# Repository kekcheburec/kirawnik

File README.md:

# kirawnik

> From Belarusian: head, manager

Compact ESP32-C6 board for powering on or rebooting a Framework Desktop over Zigbee or Wi-Fi.

## Overview

kirawnik sits between the motherboard and the case power button cable. It uses the 5V SB pin exposed on the Framework Desktop front panel connector, keeping the ESP32-C6 powered even while the system is shut down or asleep.

For easier installation, the board has silkscreen markings for the cable connections. The external antenna should be connected to the uFL (a.k.a u.FL / IPX / IPEX) connector and mounted on non-metal parts.

Firmware can be built manually or with ESPHome. With ESP32-C6 Zigbee support, the board can connect to many smart home systems and work offline.

## References

- [Front panel connector location and pinout](https://knowledgebase.frame.work/front-panel-io-connectors-amd-ryzen-ai-max-300-series-Hk3SXolHxg)
- [Framework Desktop motherboard connector schematic](https://github.com/FrameworkComputer/Framework-Desktop/blob/main/Mainboard/Mainboard_Interfaces_Schematic_Framework_Desktop_Ryzen_AI_Max.pdf)

## Disclaimer

No warranties of any kind

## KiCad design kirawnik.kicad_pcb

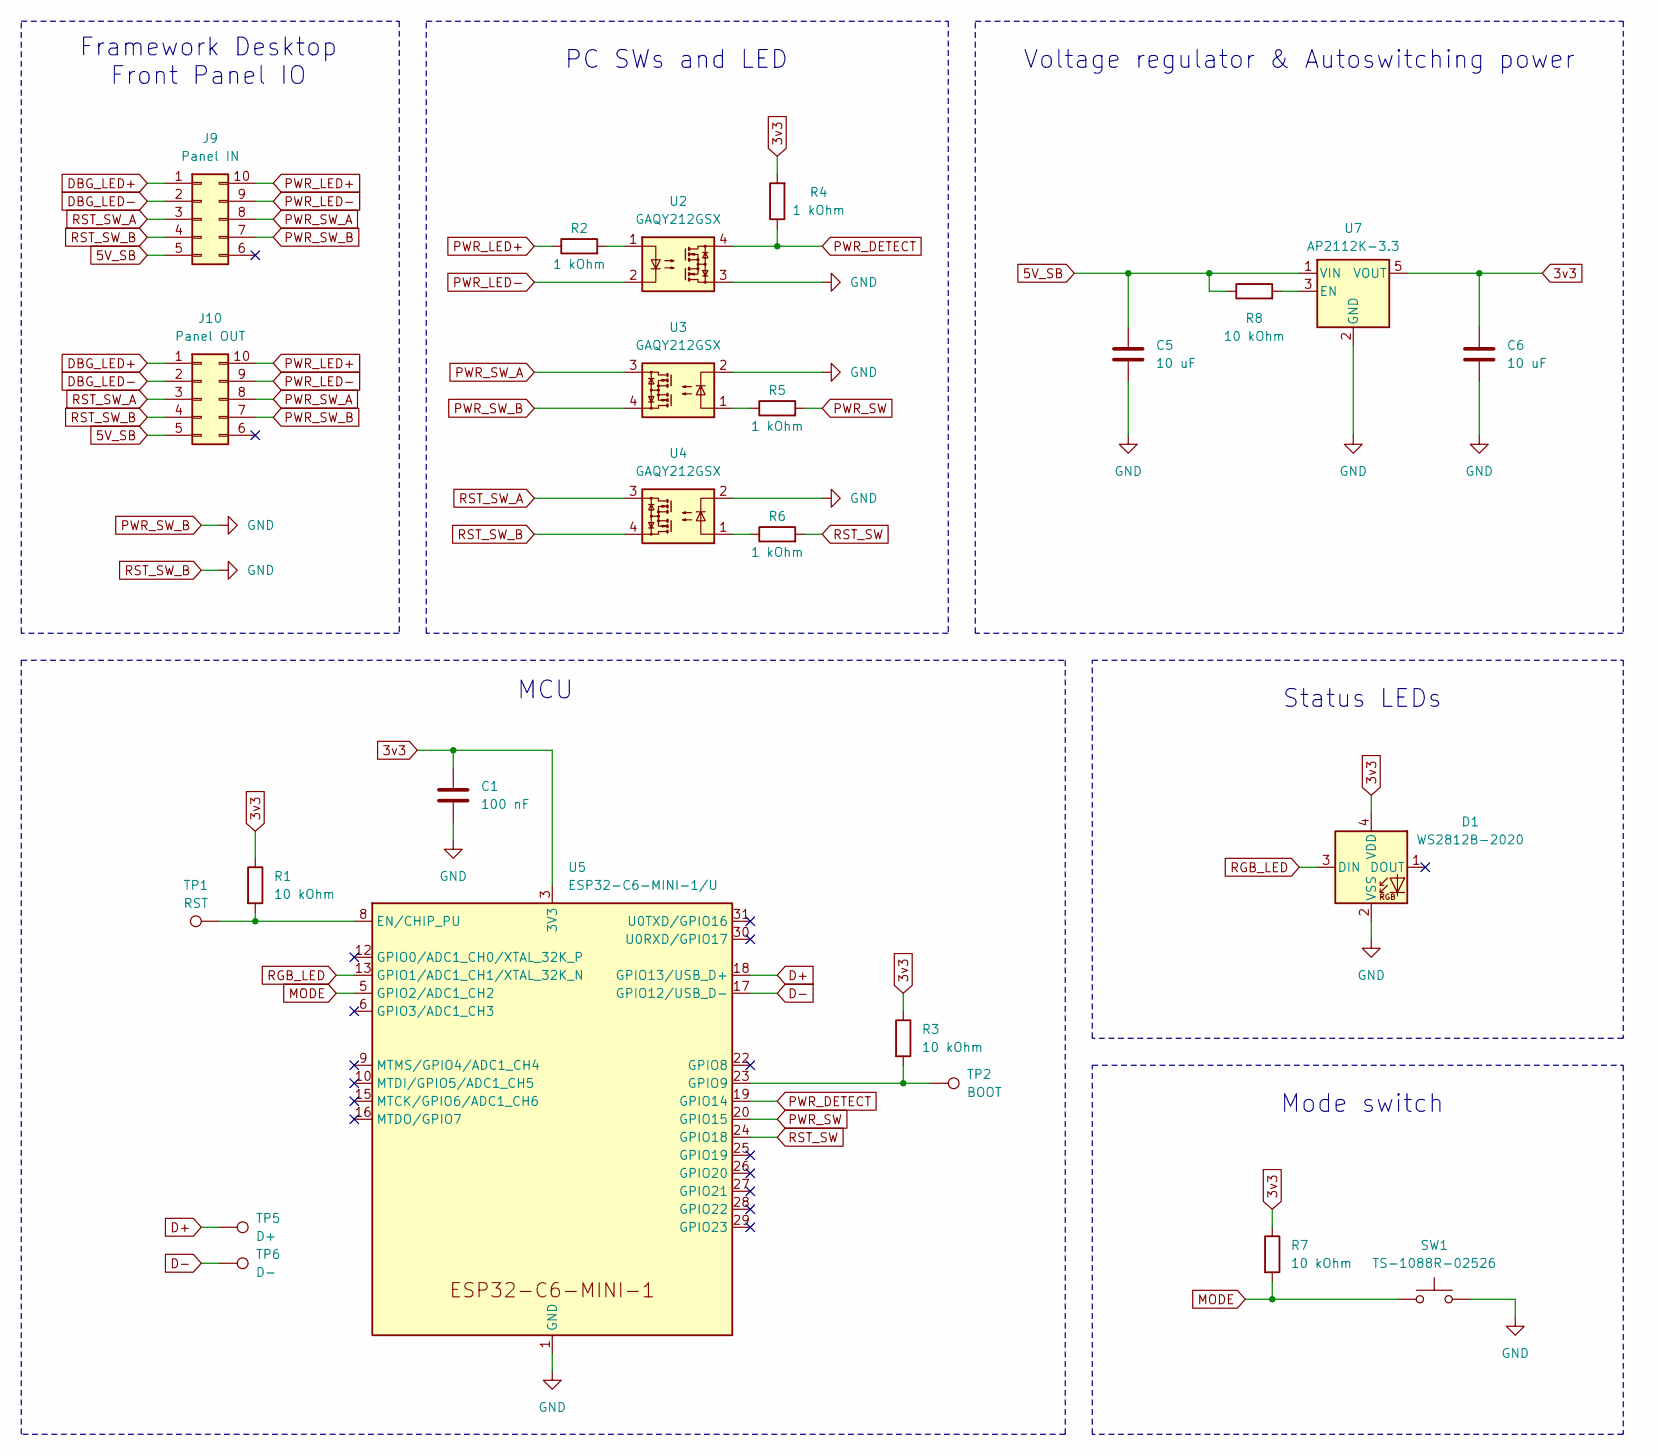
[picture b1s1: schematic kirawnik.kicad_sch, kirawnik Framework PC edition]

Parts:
C1: 100 nF; C_0402_1005Metric; LCSC Part # C1525
C5, C6: 10 uF; C_0402_1005Metric; LCSC Part # C15525
D1: WS2812B-2020; LED_WS2812B-2020_PLCC4_2.0x2.0mm; LCSC Part # C965555
J9: Panel IN; FrontIOPinSocket_2x05_P2.54mm_Horizontal
J10: Panel OUT; FrontIOPinHeader_2x05_P2.54mm_Horizontal
R1, R3, R7, R8: 10 kOhm; R_0402_1005Metric; LCSC Part # C25744
R2, R4, R5, R6: 1 kOhm; R_0402_1005Metric; LCSC Part # C11702
SW1: TS-1088R-02526; LCSC Part # C455281
TP1: RST; TestPoint_Pad_D1.0mm
TP2: BOOT; TestPoint_Pad_D1.0mm
TP5: D+; TestPoint_Pad_D1.0mm
TP6: D-; TestPoint_Pad_D1.0mm
U2, U3, U4: GAQY212GSX; SOP-4_3.8x4.1mm_P2.54mm; LCSC Part # C19271988
U5: ESP32-C6-MINI-1/U; ESP32-C6-MINI-1U; LCSC Part # C20627095
U7: AP2112K-3.3; SOT-23-5; LCSC Part # C51118

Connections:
3v3: C1.1, C6.1, D1.4 (VDD), R1.1, R3.1, R4.2, R7.1, U5.3 (3V3), U7.5 (VOUT)
5V_SB: C5.1, J9.5, J10.5, R8.1, U7.1 (VIN)
D+: TP5.1, U5.18 (GPIO13/USB_D+)
D-: TP6.1, U5.17 (GPIO12/USB_D-)
DBG_LED+: J9.1, J10.1
DBG_LED-: J9.2, J10.2
MODE: R7.2, SW1.1, U5.5 (GPIO2/ADC1_CH2)
unnamed: R2.2, U2.1
unnamed: R5.1, U3.1
unnamed: R6.1, U4.1
unnamed: R1.2, TP1.1, U5.8 (EN/CHIP_PU)
unnamed: R3.2, TP2.1, U5.23 (GPIO9)
unnamed: R8.2, U7.3 (EN)
PWR_DETECT: R4.1, U2.4, U5.19 (GPIO14)
PWR_LED+: J9.10, J10.10, R2.1
PWR_LED-: J9.9, J10.9, U2.2
PWR_SW: R5.2, U5.20 (GPIO15)
PWR_SW_A: J9.8, J10.8, U3.3
PWR_SW_B: C1.2, C5.2, C6.2, D1.2 (VSS), J9.4, J9.7, J10.4, J10.7, SW1.2, U2.3, U3.2, U3.4, U4.2, U4.4, U5.1 (GND), U5.2 (GND), U5.11 (GND), U5.14 (GND), U5.36 (GND), U5.37 (GND), U5.38 (GND), U5.39 (GND), U5.40 (GND), U5.41 (GND), U5.42 (GND), U5.43 (GND), U5.44 (GND), U5.45 (GND), U5.46 (GND), U5.47 (GND), U5.48 (GND), U5.49 (GND), U5.50 (GND), U5.51 (GND), U5.52 (GND), U5.53 (GND), U7.2 (GND)
RGB_LED: D1.3 (DIN), U5.13 (GPIO1/ADC1_CH1/XTAL_32K_N)
RST_SW: R6.2, U5.24 (GPIO18)
RST_SW_A: J9.3, J10.3, U4.3

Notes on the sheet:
MCU
Mode switch
Status LEDs
Framework Desktop Front Panel IO
Voltage regulator & Autoswitching power
PC SWs and LED

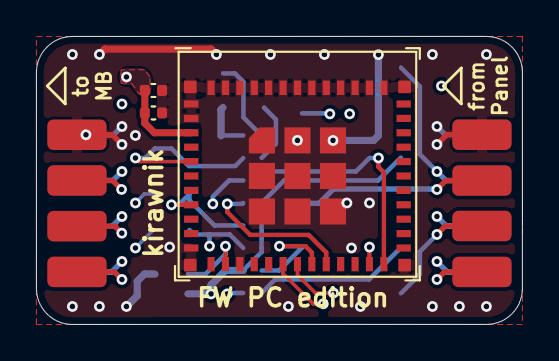
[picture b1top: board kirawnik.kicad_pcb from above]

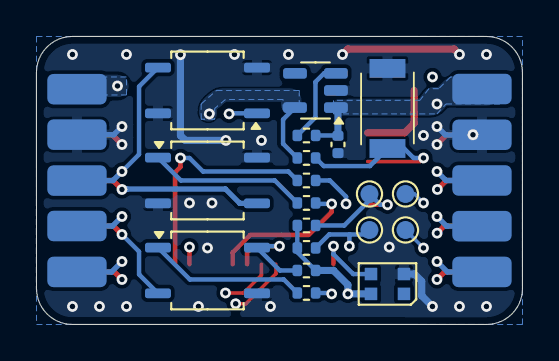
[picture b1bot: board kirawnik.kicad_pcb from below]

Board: 4 copper layers, 27.0 x 16.0 mm, 24 parts (21 on the bottom side), 22 nets.

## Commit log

2026-06-20 Add kirawnik files and other changes
2026-06-20 Update 3d model and render settings
